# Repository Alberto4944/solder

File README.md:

# solder

Description:
I made a little cat which has a photoresistor to turn on two leds when dark, and also has two leds which turn on by button.

BOM:
- 4x LED
- 5x Resistor
- 1x Photoresistor
- 1x NPM Transistor
- 1x Battery
- 2x Button

Slack Username: Albert Wu

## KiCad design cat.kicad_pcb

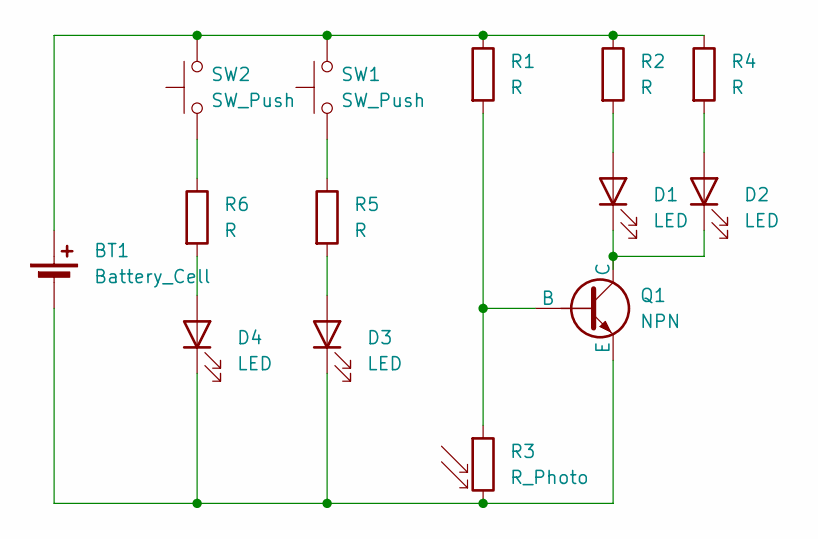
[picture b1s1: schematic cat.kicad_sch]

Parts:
BT1: Battery_Cell; BatteryHolder_Keystone_3034_1x20mm
D1, D2, D3, D4: LED; LED_D5.0mm
Q1: NPN; TO-92L_HandSolder
R1, R2, R4, R5, R6: R; R_Axial_DIN0207_L6.3mm_D2.5mm_P7.62mm_Horizontal
R3: R_Photo; R_LDR_5.1x4.3mm_P3.4mm_Vertical
SW1, SW2: SW_Push; SW_PUSH_6mm

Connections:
unnamed: BT1.1 (+), R1.1, R2.1, R4.1, SW1.2, SW2.2
unnamed: BT1.2 (-), D3.1 (K), D4.1 (K), Q1.3 (E), R3.2
unnamed: D1.2 (A), R2.2
unnamed: D1.1 (K), D2.1 (K), Q1.1 (C)
unnamed: D2.2 (A), R4.2
unnamed: D3.2 (A), R5.2
unnamed: D4.2 (A), R6.2
unnamed: Q1.2 (B), R1.2, R3.1
unnamed: R5.1, SW1.1
unnamed: R6.1, SW2.1

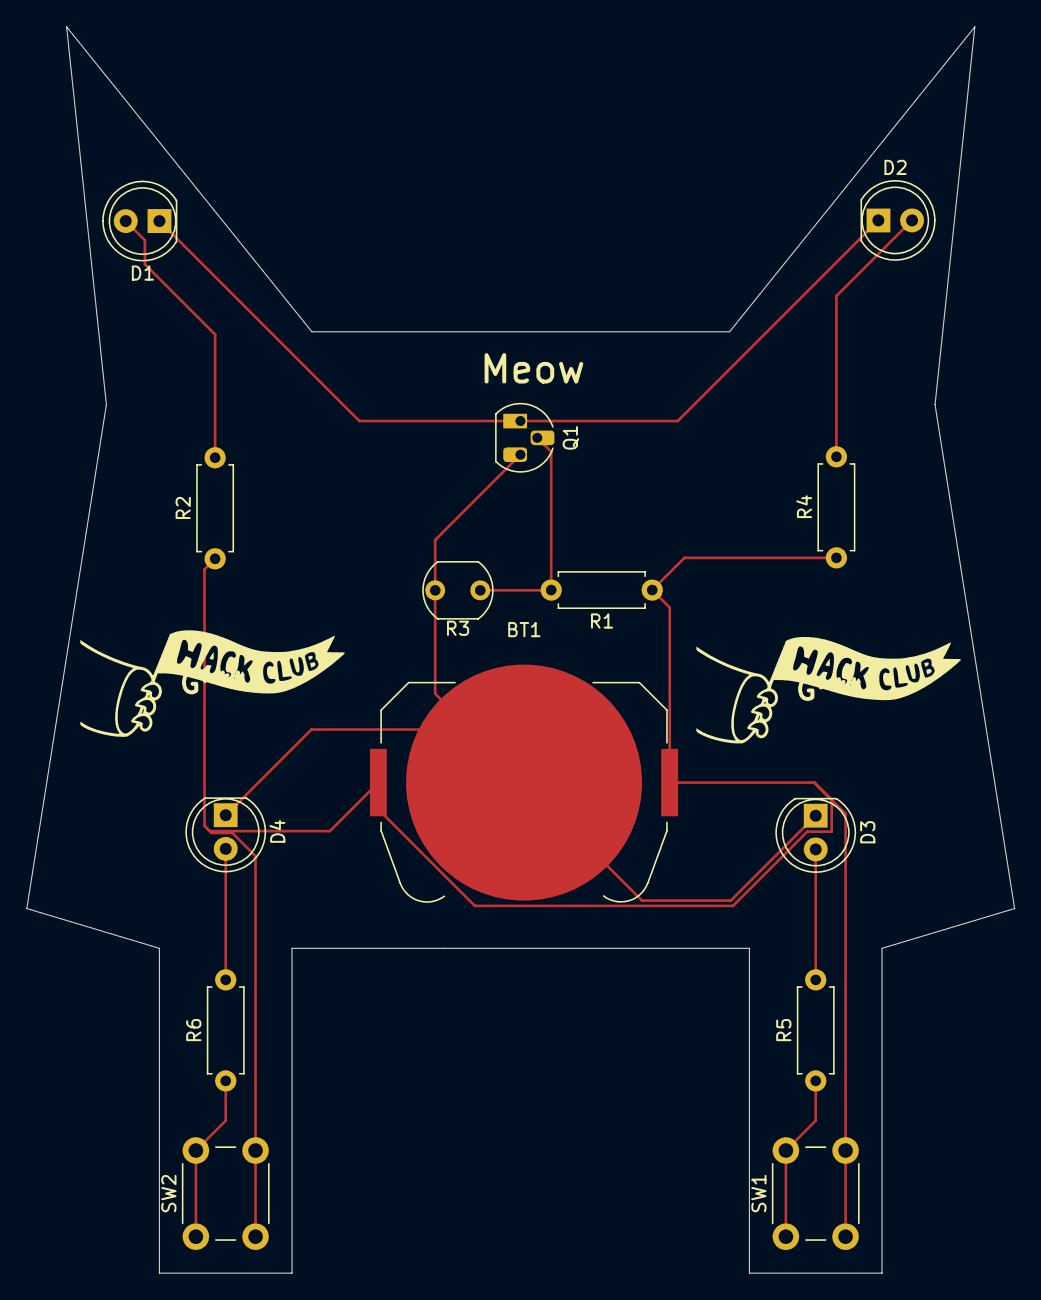
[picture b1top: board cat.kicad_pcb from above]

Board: 2 copper layers, 74.5 x 94.0 mm, 14 parts (0 on the bottom side), 10 nets.

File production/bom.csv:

Designator,Footprint,Quantity,Value,LCSC Part #
BT1,BatteryHolder_Keystone_3034_1x20mm,1,Battery_Cell,
"D1, D2, D3, D4",LED_D5.0mm,4,LED,
Q1,TO-92L_HandSolder,1,NPN,
"R1, R2, R4, R5, R6",R_Axial_DIN0207_L6.3mm_D2.5mm_P7.62mm_Horizontal,5,R,
R3,R_LDR_5.1x4.3mm_P3.4mm_Vertical,1,R_Photo,
"SW1, SW2",SW_PUSH_6mm,2,SW_Push,

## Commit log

2025-07-01 add more silkscreen
